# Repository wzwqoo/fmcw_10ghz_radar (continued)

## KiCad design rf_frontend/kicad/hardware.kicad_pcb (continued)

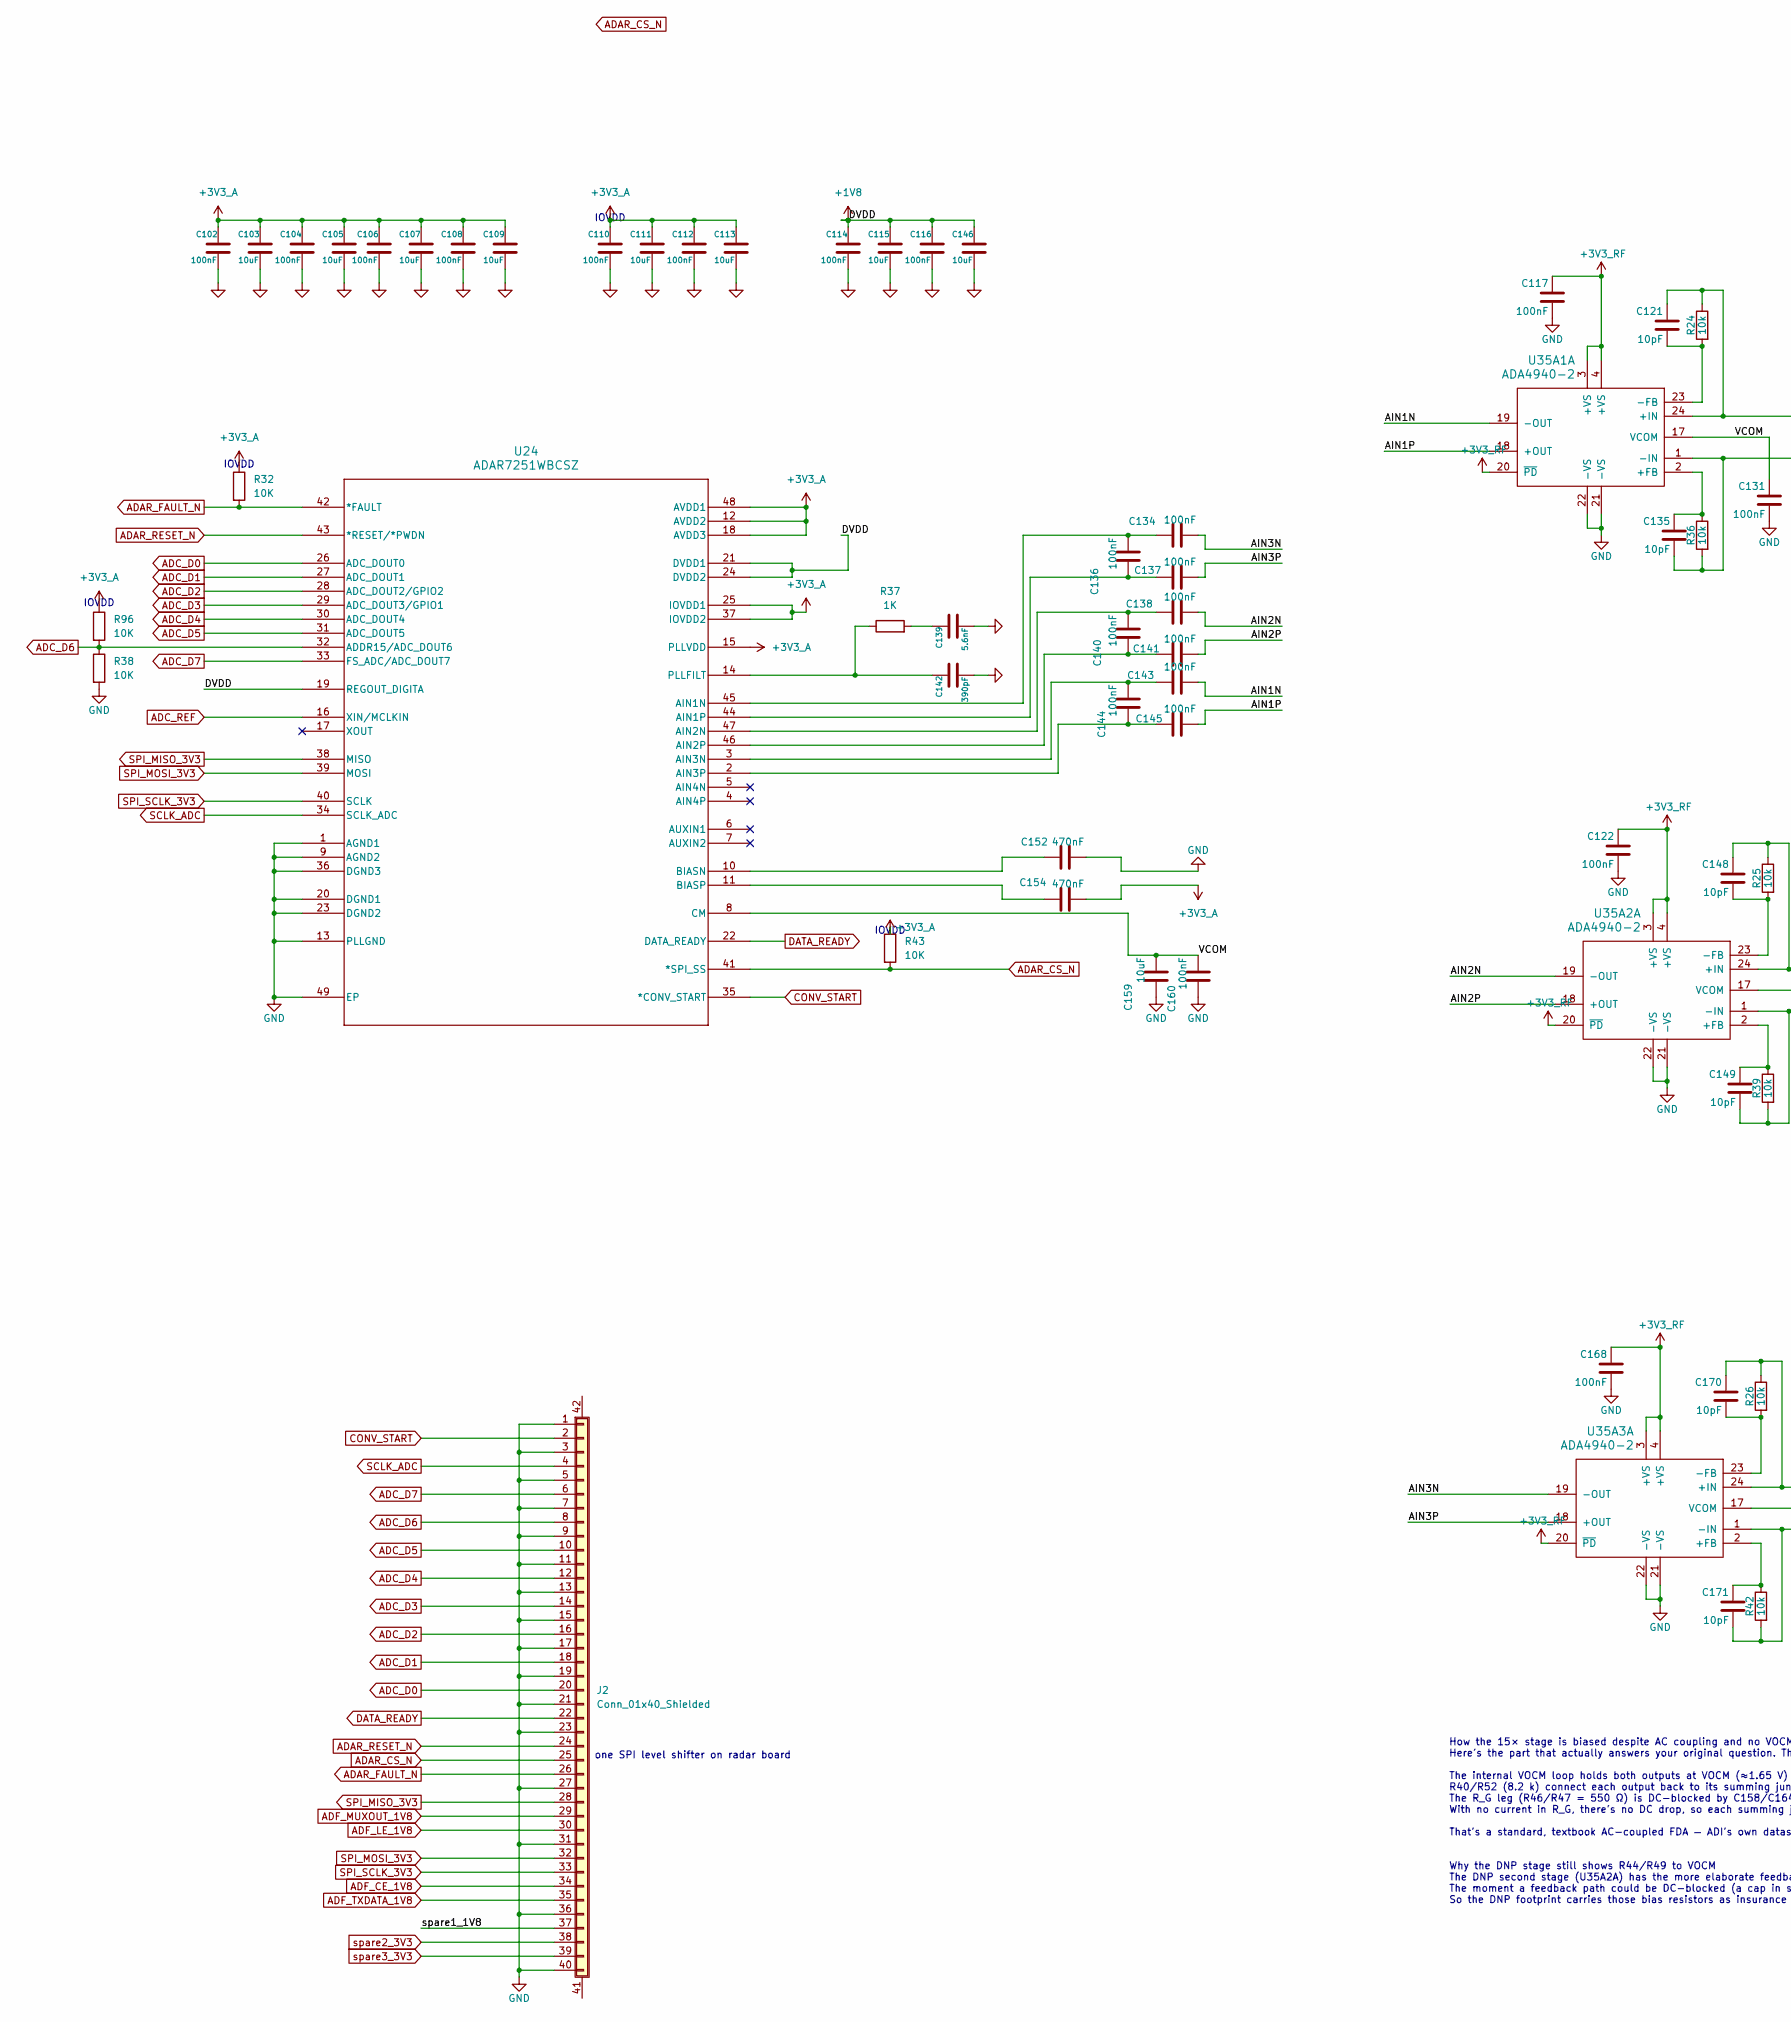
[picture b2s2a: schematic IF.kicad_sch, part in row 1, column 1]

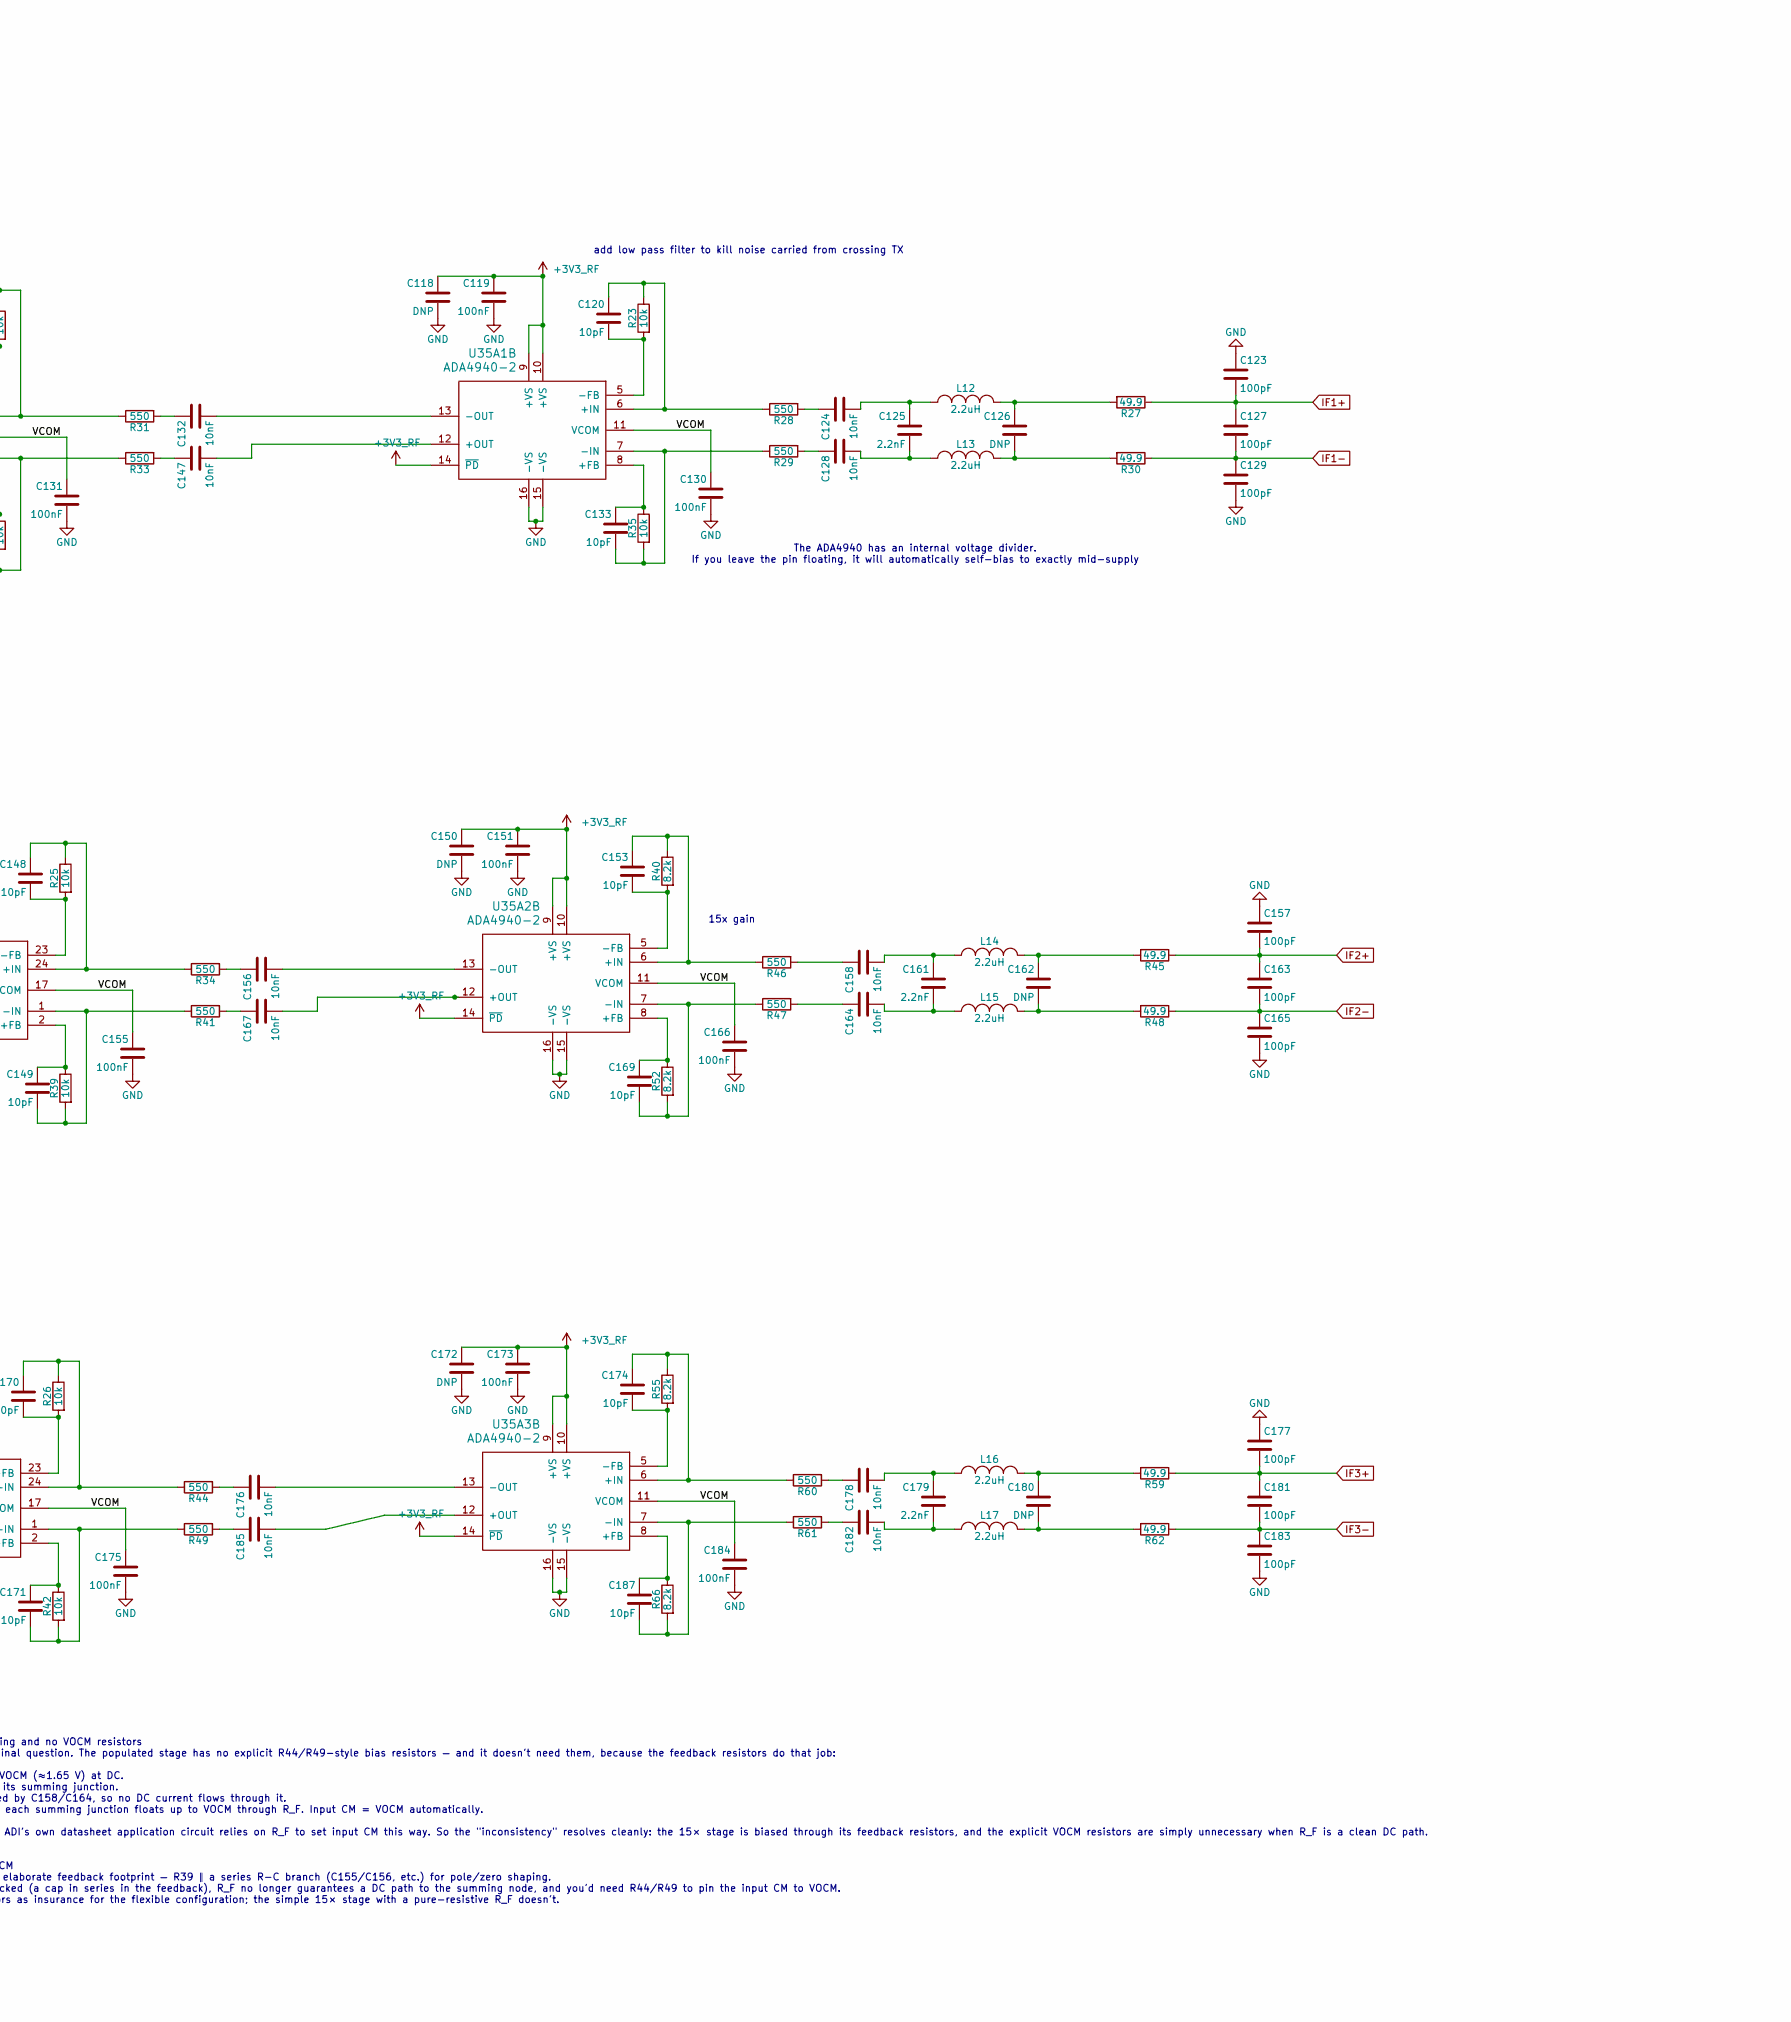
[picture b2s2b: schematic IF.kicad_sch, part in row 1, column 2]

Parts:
C102, C104, C106, C108, C110, C112, C114, C116, C117, C119, C122, C130, C131, C134, C136, C137, C138, C140, C141, C143, C144, C145, C151, C155, C160, C166, C168, C173, C175, C184: 100nF; C_0402_1005Metric
C103, C105, C107, C109, C111, C113, C115, C146, C159: 10uF; C_0805_2012Metric
C118, C126, C150, C162, C172, C180: DNP; C_0402_1005Metric
C120, C121, C133, C135, C148, C149, C153, C169, C170, C171, C174, C187: 10pF; C_0402_1005Metric
C123, C127, C129, C157, C163, C165, C177, C181, C183: 100pF; C_0402_1005Metric
C124, C128, C132, C147, C156, C158, C164, C167, C176, C178, C182, C185: 10nF; C_0402_1005Metric
C125, C161, C179: 2.2nF; C_0402_1005Metric
C139: 5.6nF; C_0402_1005Metric
C142: 390pF; C_0402_1005Metric
C152, C154: 470nF; C_0402_1005Metric
J2: Conn_01x40_Shielded; FPC-SMD_40P-P0.50_XUNPU_FPC-05FB-40PH20; Part# FPC-05FB-40PH20; LCSC Part # C2856837
L12, L13, L14, L15, L16, L17: 2.2uH; L_0805_2012Metric
R23, R24, R25, R26, R35, R36, R39, R42: 10k; R_0402_1005Metric
R27, R30, R45, R48, R59, R62: 49.9; R_0402_1005Metric
R28, R29, R31, R33, R34, R41, R44, R46, R47, R49, R60, R61: 550; R_0402_1005Metric
R32, R38, R43, R96: 10K; R_0402_1005Metric
R37: 1K; R_0402_1005Metric
R40, R52, R55, R66: 8.2k; R_0402_1005Metric
U24: ADAR7251WBCSZ; LFCSP-VQ-48-1EP_7x7mm_P0.5mm
U35A1, U35A2, U35A3: ADA4940-2; LFCSP-24-1EP_4x4mm_P0.5mm_EP2.5x2.5mm

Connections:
+1V8: C114.1, C115.1, C116.1, C146.1, U24.19 (REGOUT_DIGITA), U24.21 (DVDD1), U24.24 (DVDD2); also elsewhere on the board
+3V3_A: C102.1, C103.1, C104.1, C105.1, C106.1, C107.1, C108.1, C109.1, C110.1, C111.1, C112.1, C113.1, C154.2, R32.1, R43.1, R96.1, U24.12 (AVDD2), U24.15 (PLLVDD), U24.18 (AVDD3), U24.25 (IOVDD1), U24.37 (IOVDD2), U24.48 (AVDD1); also elsewhere on the board
+3V3_RF: C117.1, C118.1, C119.1, C122.1, C150.1, C151.1, C168.1, C172.1, C173.1, U35A1.3 (+VS), U35A1.4 (+VS), U35A1.9 (+VS), U35A1.10 (+VS), U35A1.14 (~PD), U35A1.20 (~PD), U35A2.3 (+VS), U35A2.4 (+VS), U35A2.9 (+VS), U35A2.10 (+VS), U35A2.14 (~PD), U35A2.20 (~PD), U35A3.3 (+VS), U35A3.4 (+VS), U35A3.9 (+VS), U35A3.10 (+VS), U35A3.14 (~PD), U35A3.20 (~PD); also elsewhere on the board
/IF/AIN1N: C143.2, U35A1.19 (-OUT)
/IF/AIN1P: C145.2, U35A1.18 (+OUT)
/IF/AIN2N: C138.2, U35A2.19 (-OUT)
/IF/AIN2P: C141.2, U35A2.18 (+OUT)
/IF/AIN3N: C134.2, U35A3.19 (-OUT)
/IF/AIN3P: C137.2, U35A3.18 (+OUT)
/IF/VCOM: C130.1, C131.1, C155.1, C159.2, C160.2, C166.1, C175.1, C184.1, U24.8 (CM), U35A1.11 (VCOM), U35A1.17 (VCOM), U35A2.11 (VCOM), U35A2.17 (VCOM), U35A3.11 (VCOM), U35A3.17 (VCOM)
/IF/spare1_1V8: J2.37
ADAR_CS_N: J2.25, R43.2, U24.41 (*SPI_SS)
ADAR_FAULT_N: J2.26, R32.2, U24.42 (*FAULT)
ADAR_RESET_N: J2.24, U24.43 (*RESET/*PWDN)
ADC_D0: J2.20, U24.26 (ADC_DOUT0)
ADC_D1: J2.18, U24.27 (ADC_DOUT1)
ADC_D2: J2.16, U24.28 (ADC_DOUT2/GPIO2)
ADC_D3: J2.14, U24.29 (ADC_DOUT3/GPIO1)
ADC_D4: J2.12, U24.30 (ADC_DOUT4)
ADC_D5: J2.10, U24.31 (ADC_DOUT5)
ADC_D6: J2.8, R38.1, R96.2, U24.32 (ADDR15/ADC_DOUT6)
ADC_D7: J2.6, U24.33 (FS_ADC/ADC_DOUT7)
ADC_REF: U24.16 (XIN/MCLKIN); also elsewhere on the board
ADF_CE_1V8: J2.34; also elsewhere on the board
ADF_LE_1V8: J2.30; also elsewhere on the board
ADF_MUXOUT_1V8: J2.29; also elsewhere on the board
ADF_TXDATA_1V8: J2.35; also elsewhere on the board
CONV_START: J2.2, U24.35 (*CONV_START)
DATA_READY: J2.22, U24.22 (DATA_READY)
GND: C102.2, C103.2, C104.2, C105.2, C106.2, C107.2, C108.2, C109.2, C110.2, C111.2, C112.2, C113.2, C114.2, C115.2, C116.2, C117.2, C118.2, C119.2, C122.2, C123.1, C129.2, C130.2, C131.2, C139.2, C142.2, C146.2, C150.2, C151.2, C152.2, C155.2, C157.1, C159.1, C160.1, C165.2, C166.2, C168.2, C172.2, C173.2, C175.2, C177.1, C183.2, C184.2, J2.1, J2.3, J2.5, J2.7, J2.9, J2.11, J2.13, J2.15, J2.17, J2.19, J2.21, J2.23, J2.27, J2.31, J2.36, J2.40, R38.2, U24.1 (AGND1), U24.9 (AGND2), U24.13 (PLLGND), U24.20 (DGND1), U24.23 (DGND2), U24.36 (DGND3), U24.49 (EP), U35A1.15 (-VS), U35A1.16 (-VS), U35A1.21 (-VS), U35A1.22 (-VS), U35A1.25, U35A2.15 (-VS), U35A2.16 (-VS), U35A2.21 (-VS), U35A2.22 (-VS), U35A2.25, U35A3.15 (-VS), U35A3.16 (-VS), U35A3.21 (-VS), U35A3.22 (-VS), U35A3.25; also elsewhere on the board
IF1+: C123.2, C127.1, R27.1; also elsewhere on the board
IF1-: C127.2, C129.1, R30.1; also elsewhere on the board
IF2+: C157.2, C163.1, R45.1; also elsewhere on the board
IF2-: C163.2, C165.1, R48.1; also elsewhere on the board
IF3+: C177.2, C181.1, R59.1; also elsewhere on the board
IF3-: C181.2, C183.1, R62.1; also elsewhere on the board
unnamed: C124.1, R28.2
unnamed: C124.2, C125.1, L12.2
unnamed: C125.2, C128.2, L13.2
unnamed: C126.1, L12.1, R27.2
unnamed: C126.2, L13.1, R30.2
unnamed: C128.1, R29.2
unnamed: C132.1, R31.2
unnamed: C139.1, R37.2
unnamed: C147.1, R33.2
unnamed: C156.1, R34.2
unnamed: C158.1, R46.2
unnamed: C158.2, C161.1, L14.2
unnamed: C161.2, C164.2, L15.2
unnamed: C162.1, L14.1, R45.2
unnamed: C162.2, L15.1, R48.2
unnamed: C164.1, R47.2
unnamed: C167.1, R41.2
unnamed: C176.1, R44.2
unnamed: C178.1, R60.2
unnamed: C178.2, C179.1, L16.2
unnamed: C179.2, C182.2, L17.2
unnamed: C180.1, L16.1, R59.2
unnamed: C180.2, L17.1, R62.2
unnamed: C182.1, R61.2
unnamed: C185.1, R49.2
unnamed: C134.1, C136.2, U24.45 (AIN1N)
unnamed: C136.1, C137.1, U24.44 (AIN1P)
unnamed: C138.1, C140.2, U24.47 (AIN2N)
unnamed: C140.1, C141.1, U24.46 (AIN2P)
unnamed: C143.1, C144.2, U24.3 (AIN3N)
unnamed: C144.1, C145.1, U24.2 (AIN3P)
unnamed: C152.1, U24.10 (BIASN)
unnamed: C154.1, U24.11 (BIASP)
unnamed: C142.1, R37.1, U24.14 (PLLFILT)
unnamed: C135.1, R36.1, U35A1.2 (+FB)
unnamed: C121.1, R24.1, R31.1, U35A1.24 (+IN)
unnamed: C121.2, R24.2, U35A1.23 (-FB)
unnamed: C135.2, R33.1, R36.2, U35A1.1 (-IN)
unnamed: C133.1, R35.1, U35A1.8 (+FB)
unnamed: C120.1, R23.1, R28.1, U35A1.6 (+IN)
unnamed: C147.2, U35A1.12 (+OUT)
unnamed: C120.2, R23.2, U35A1.5 (-FB)
unnamed: C133.2, R29.1, R35.2, U35A1.7 (-IN)
unnamed: C132.2, U35A1.13 (-OUT)
unnamed: C149.1, R39.1, U35A2.2 (+FB)
unnamed: C148.1, R25.1, R34.1, U35A2.24 (+IN)
unnamed: C148.2, R25.2, U35A2.23 (-FB)
unnamed: C149.2, R39.2, R41.1, U35A2.1 (-IN)
unnamed: C169.1, R52.1, U35A2.8 (+FB)
unnamed: C153.1, R40.1, R46.1, U35A2.6 (+IN)
unnamed: C167.2, U35A2.12 (+OUT)
unnamed: C153.2, R40.2, U35A2.5 (-FB)
unnamed: C169.2, R47.1, R52.2, U35A2.7 (-IN)
unnamed: C156.2, U35A2.13 (-OUT)
unnamed: C171.1, R42.1, U35A3.2 (+FB)
unnamed: C170.1, R26.1, R44.1, U35A3.24 (+IN)
unnamed: C170.2, R26.2, U35A3.23 (-FB)
unnamed: C171.2, R42.2, R49.1, U35A3.1 (-IN)
unnamed: C187.1, R66.1, U35A3.8 (+FB)
unnamed: C174.1, R55.1, R60.1, U35A3.6 (+IN)
unnamed: C185.2, U35A3.12 (+OUT)
unnamed: C174.2, R55.2, U35A3.5 (-FB)
unnamed: C187.2, R61.1, R66.2, U35A3.7 (-IN)
unnamed: C176.2, U35A3.13 (-OUT)
SCLK_ADC: J2.4, U24.34 (SCLK_ADC)
SPI_MISO_3V3: J2.28, U24.38 (MISO)
SPI_MOSI_3V3: J2.32, U24.39 (MOSI); also elsewhere on the board
SPI_SCLK_3V3: J2.33, U24.40 (SCLK); also elsewhere on the board
spare2_3V3: J2.38
spare3_3V3: J2.39

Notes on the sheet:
add low pass filter to kill noise carried from crossing TX
IOVDD
The ADA4940 has an internal voltage divider. If you leave the pin floating, it will automatically self-bias to exactly mid-supply
15x gain
How the 15× stage is biased despite AC coupling and no VOCM resistors Here's the part that actually answers your original question. The populated stage has no explicit R44/R49-style bias resistors — and it doesn't need them, because the feedback resistors do that job: The internal VOCM loop holds b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
one SPI level shifter on radar board

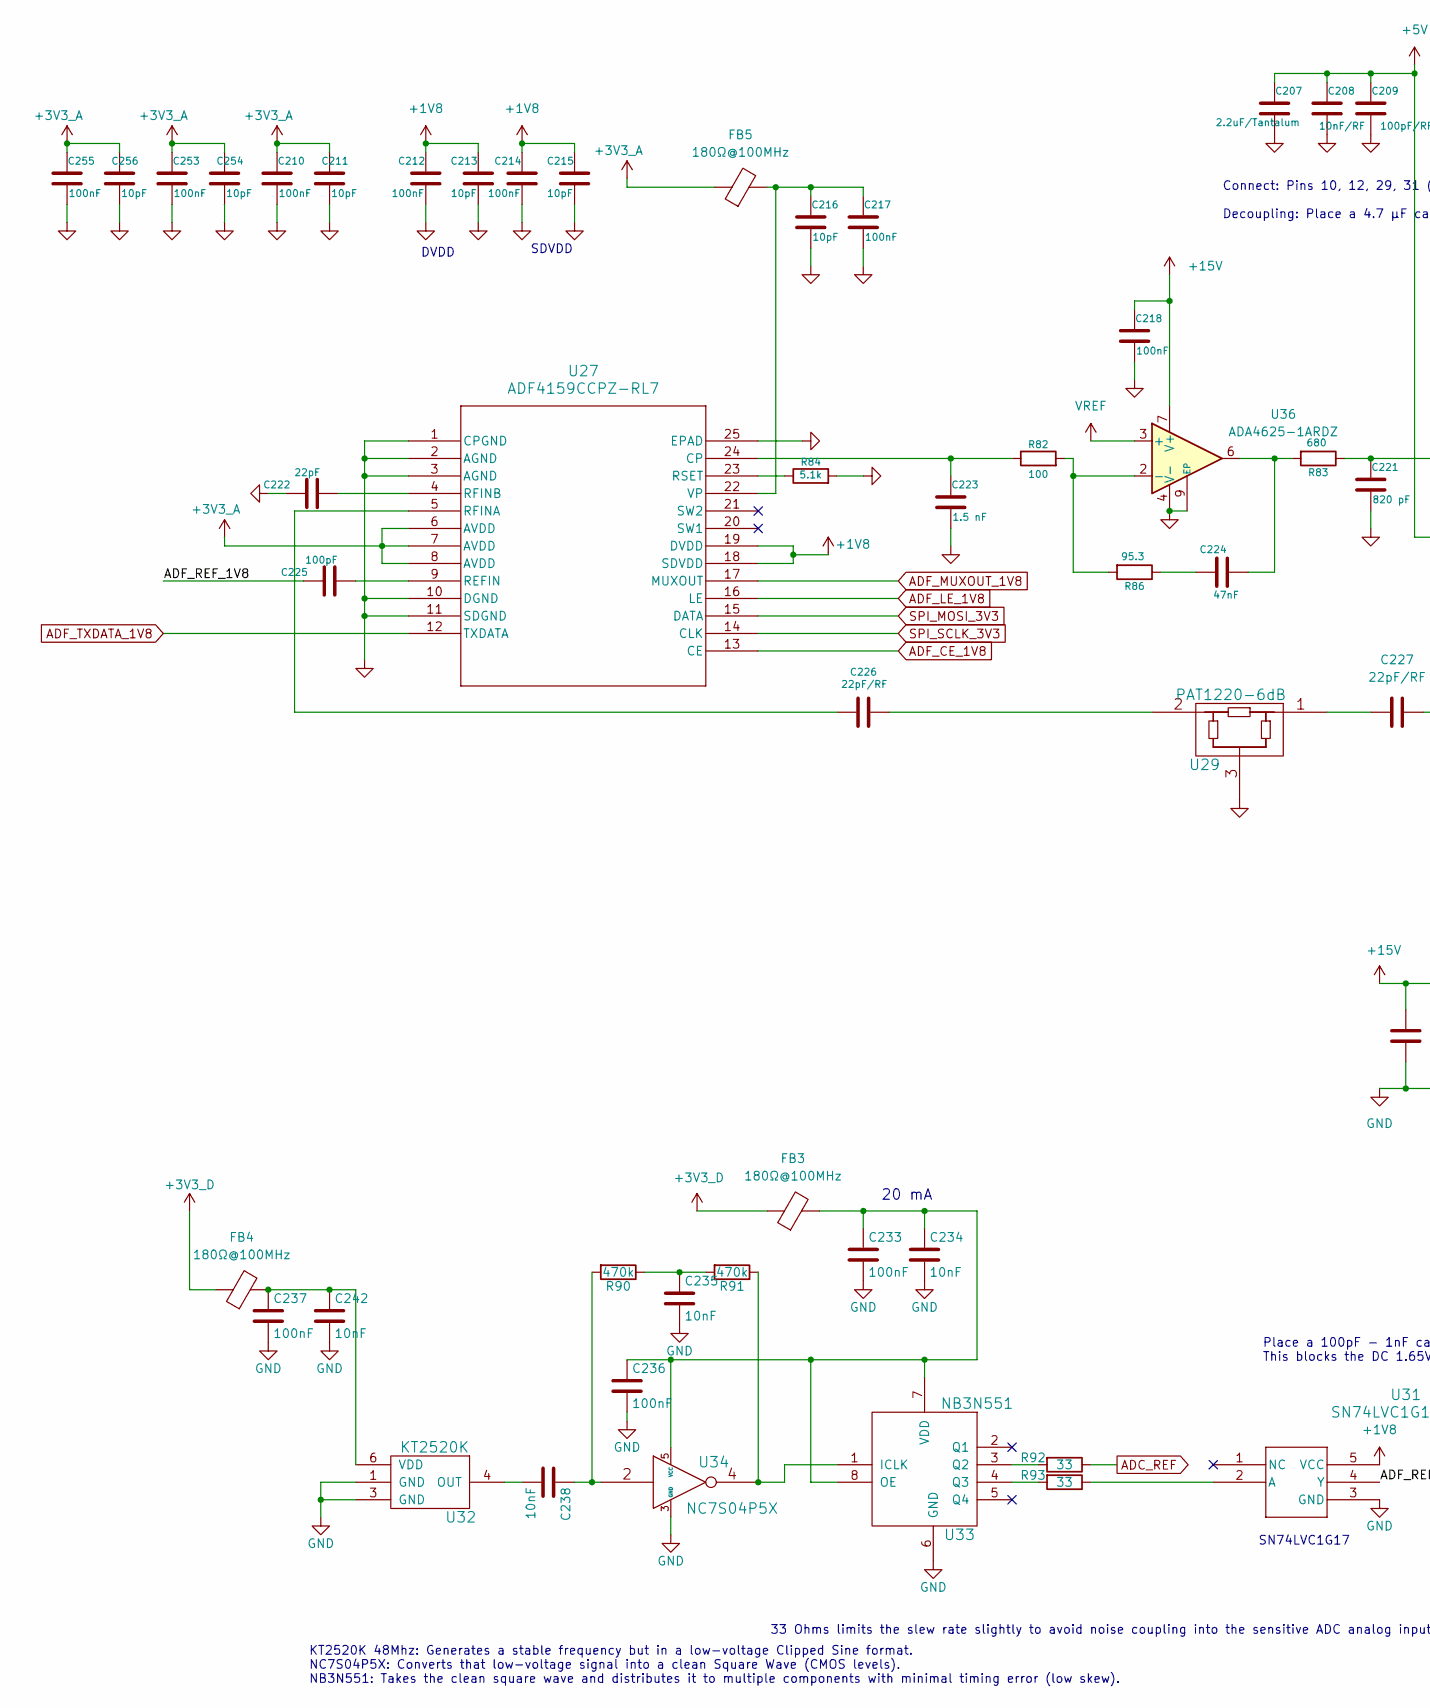
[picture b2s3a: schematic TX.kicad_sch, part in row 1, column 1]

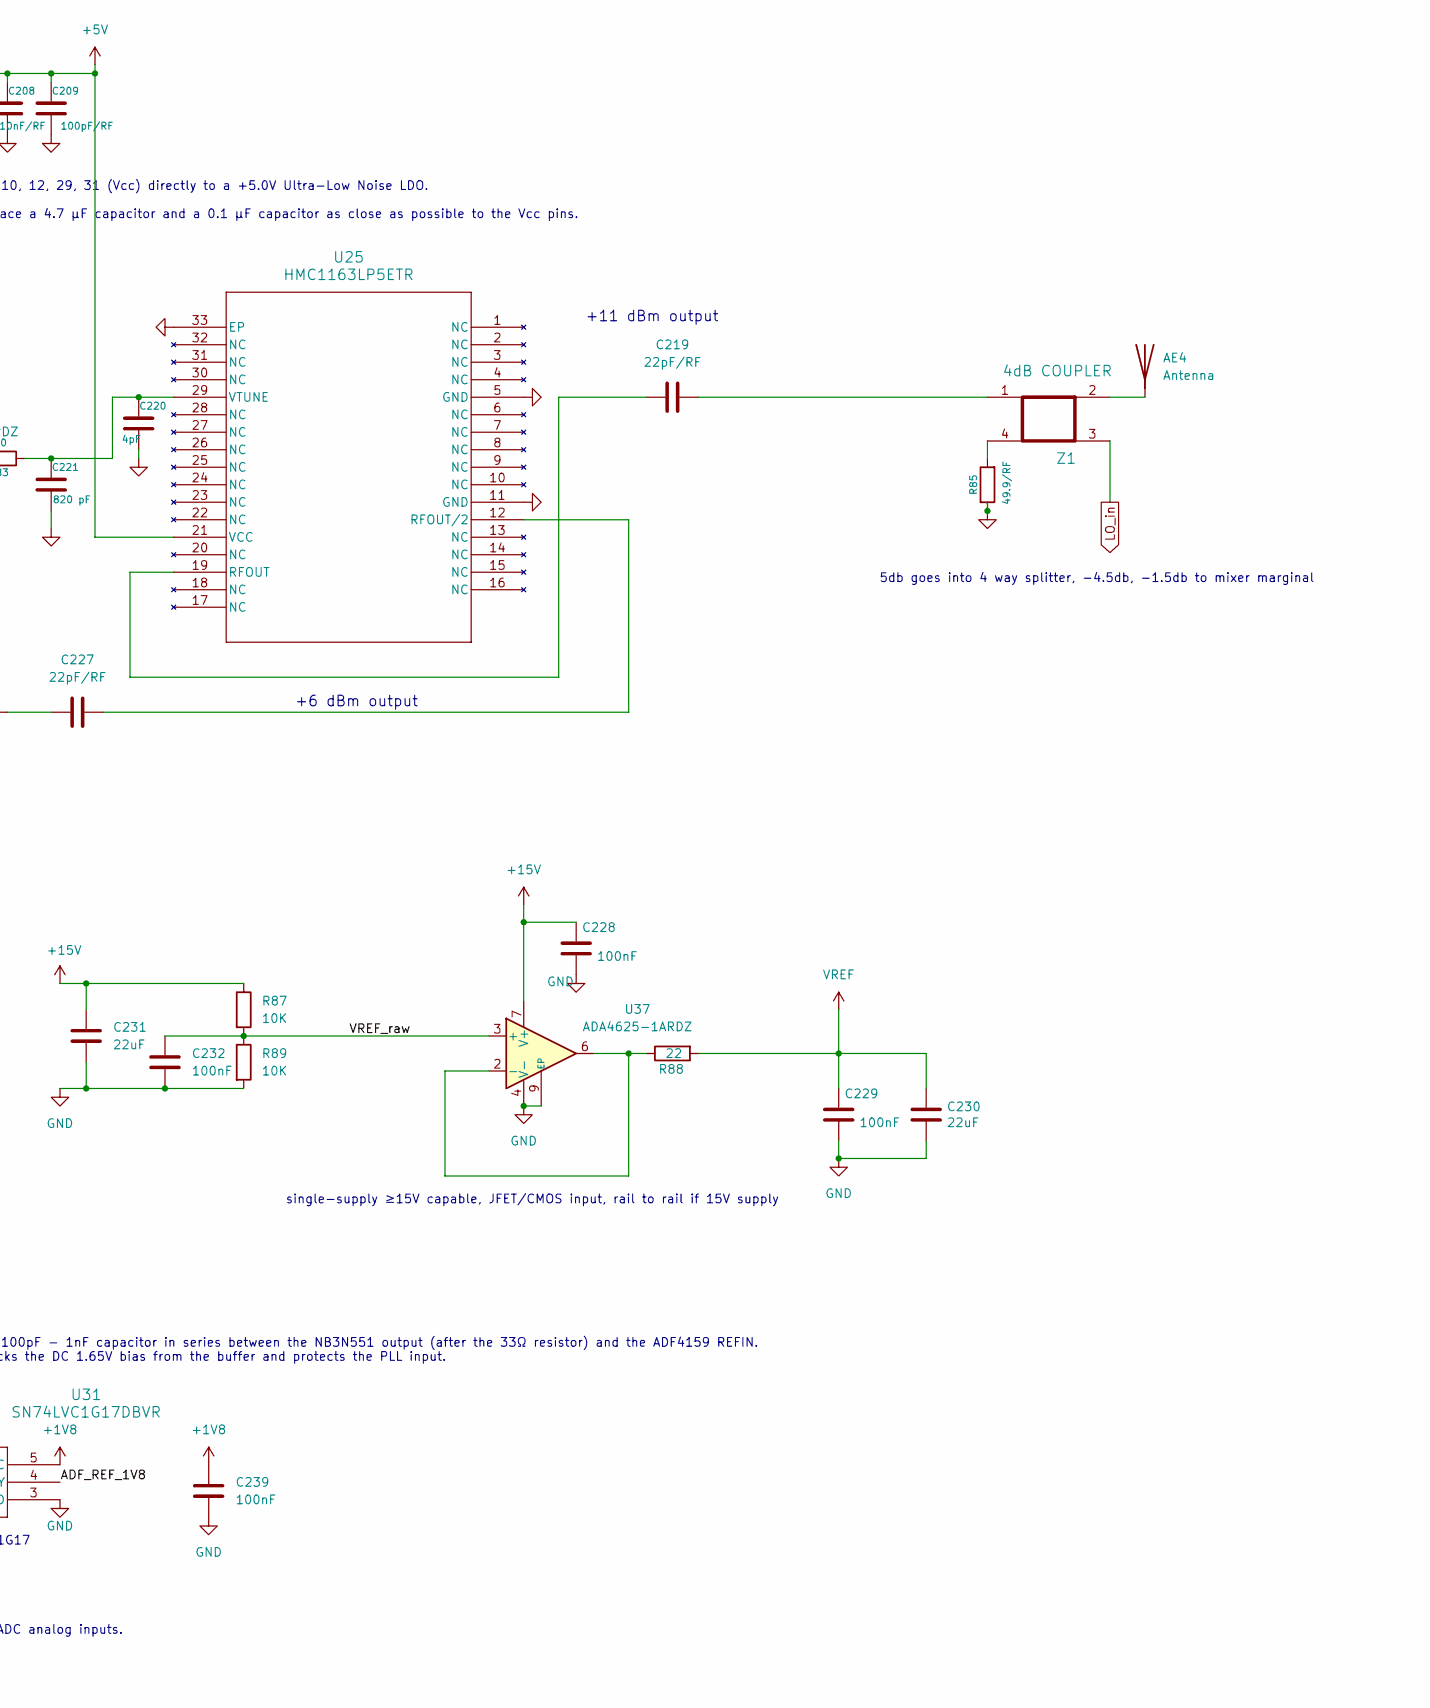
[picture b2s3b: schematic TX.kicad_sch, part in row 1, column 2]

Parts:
AE4: Antenna; antenna
C207: 2.2uF/Tantalum; C_0805_2012Metric
C208: 10nF/RF; C_0402_1005Metric
C209: 100pF/RF; C_0402_1005Metric
C210, C212, C214, C217, C218, C228, C229, C232, C233, C236, C237, C239, C253, C255: 100nF; C_0402_1005Metric
C211, C213, C215, C216, C254, C256: 10pF; C_0402_1005Metric
C219, C226, C227: 22pF/RF; C_0201_0603Metric
C220: 4pF; C_0402_1005Metric
C221: 820 pF; C_0402_1005Metric
C222: 22pF; C_0402_1005Metric
C223: 1.5 nF; C_0402_1005Metric
C224: 47nF; C_0402_1005Metric
C225: 100pF; C_0402_1005Metric
C230, C231: 22uF; C_0805_2012Metric
C234, C235, C238, C242: 10nF; C_0402_1005Metric
FB3, FB4, FB5: 180Ω@100MHz; L_0603_1608Metric; Part# BLM18PG181SN1D; LCSC Part # C82850
R82: 100; R_0402_1005Metric
R83: 680; R_0402_1005Metric
R84: 5.1k; R_0402_1005Metric
R85: 49.9/RF; R_0402_1005Metric
R86: 95.3; R_0402_1005Metric
R87, R89: 10K; R_0402_1005Metric; LCSC Part # x
R88: 22; R_0805_2012Metric; LCSC Part # C108406
R90, R91: 470k; R_0402_1005Metric
R92, R93: 33; R_0805_2012Metric
U25: HMC1163LP5ETR; LFCSP-32-1EP_5x5mm_P0.5mm_EP3.1x3.1mm
U27: ADF4159CCPZ-RL7; LFCSP-24-1EP_4x4mm_P0.5mm_EP2.3x2.3mm
U29: PAT1220-6dB; ATTN_PAT1220-C-1DB-T5
U31: SN74LVC1G17DBVR; SOT-23-5
U32: KT2520K; Oscillator_SMD_Kyocera_2520-6Pin_2.5x2.0mm
U33: NB3N551; DFN-8-1EP_6x5mm_P1.27mm_EP4x4mm
U34: NC7S04P5X; SOT-353_SC-70-5
U36, U37: ADA4625-1ARDZ; SOIC-8-1EP_3.9x4.9mm_P1.27mm_EP2.29x3mm
Z1: 4dB COUPLER; branchline

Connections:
+1V8: C212.1, C213.1, C214.1, C215.1, C239.1, U27.18 (SDVDD), U27.19 (DVDD), U31.5 (VCC); also elsewhere on the board
+3V3_A: C210.1, C211.1, C253.1, C254.1, C255.1, C256.1, FB5.1, U27.6 (AVDD), U27.7 (AVDD), U27.8 (AVDD); also elsewhere on the board
+3V3_D: FB3.1, FB4.1; also elsewhere on the board
+5V: C207.1, C208.1, C209.1, U25.21 (VCC); also elsewhere on the board
+15V: C218.1, C228.1, C231.1, R87.1, U36.7 (V+), U37.7 (V+); also elsewhere on the board
/TX/ADF_REF_1V8: C225.1, U31.4 (Y)
/TX/VREF_raw: C232.1, R87.2, R89.1, U37.3 (+)
ADC_REF: R92.1; also elsewhere on the board
ADF_CE_1V8: U27.13 (CE); also elsewhere on the board
ADF_LE_1V8: U27.16 (LE); also elsewhere on the board
ADF_MUXOUT_1V8: U27.17 (MUXOUT); also elsewhere on the board
ADF_TXDATA_1V8: U27.12 (TXDATA); also elsewhere on the board
GND: C207.2, C208.2, C209.2, C210.2, C211.2, C212.2, C213.2, C214.2, C215.2, C216.2, C217.2, C218.2, C220.2, C221.2, C222.1, C223.2, C228.2, C229.2, C230.2, C231.2, C232.2, C233.2, C234.2, C235.2, C236.2, C237.2, C239.2, C242.2, C253.2, C254.2, C255.2, C256.2, R84.2, R85.1, R89.2, U25.5 (GND), U25.11 (GND), U25.33 (EP), U27.1 (CPGND), U27.2 (AGND), U27.3 (AGND), U27.10 (DGND), U27.11 (SDGND), U27.25 (EPAD), U29.3, U31.3 (GND), U32.1 (GND), U32.3 (GND), U33.6 (GND), U34.3 (GND), U36.4 (V-), U36.9 (EP), U37.4 (V-), U37.9 (EP); also elsewhere on the board
LO_in: Z1.3; also elsewhere on the board
unnamed: AE4.1 (A_1), Z1.2
unnamed: C219.2, Z1.1
unnamed: C224.1, R86.1
unnamed: C224.2, R83.2, U36.6
unnamed: C226.1, U29.2
unnamed: C227.1, U29.1
unnamed: C235.1, R90.1, R91.2
unnamed: C238.1, R90.2, U34.2
unnamed: R85.2, Z1.4
unnamed: C219.1, U25.19 (RFOUT)
unnamed: C227.2, U25.12 (RFOUT/2)
unnamed: C220.1, C221.1, R83.1, U25.29 (VTUNE)
unnamed: C223.1, R82.1, U27.24 (CP)
unnamed: C225.2, U27.9 (REFIN)
unnamed: C226.2, U27.5 (RFINA)
unnamed: C222.2, U27.4 (RFINB)
unnamed: R84.1, U27.23 (RSET)
unnamed: C216.1, C217.1, FB5.2, U27.22 (VP)
unnamed: R93.1, U31.2 (A)
unnamed: C238.2, U32.4 (OUT)
unnamed: C237.1, C242.1, FB4.2, U32.6 (VDD)
unnamed: R91.1, U33.1 (ICLK), U34.4
unnamed: C233.1, C234.1, C236.1, FB3.2, U33.7 (VDD), U33.8 (OE), U34.5 (VCC)
unnamed: R92.2, U33.3 (Q2)
unnamed: R93.2, U33.4 (Q3)
unnamed: R82.2, R86.2, U36.2 (-)
unnamed: R88.1, U37.2 (-), U37.6
SPI_MOSI_3V3: U27.15 (DATA); also elsewhere on the board
SPI_SCLK_3V3: U27.14 (CLK); also elsewhere on the board
VREF: C229.1, C230.1, R88.2, U36.3 (+)

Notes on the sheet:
Connect: Pins 10, 12, 29, 31 (Vcc) directly to a +5.0V Ultra-Low Noise LDO. Decoupling: Place a 4.7 µF capacitor and a 0.1 µF capacitor as close as possible to the Vcc pins.
33 Ohms limits the slew rate slightly to avoid noise coupling into the sensitive ADC analog inputs.
Place a 100pF - 1nF capacitor in series between the NB3N551 output (after the 33Ω resistor) and the ADF4159 REFIN. This blocks the DC 1.65V bias from the buffer and protects the PLL input.
SN74LVC1G17
single-supply ≥15V capable, JFET/CMOS input, rail to rail if 15V supply
DVDD
KT2520K 48Mhz: Generates a stable frequency but in a low-voltage Clipped Sine format. NC7S04P5X: Converts that low-voltage signal into a clean Square Wave (CMOS levels). NB3N551: Takes the clean square wave and distributes it to multiple components with minimal timing error (low skew).
+11 dBm output
+6 dBm output
SDVDD
5db goes into 4 way splitter, -4.5db, -1.5db to mixer marginal
20 mA
